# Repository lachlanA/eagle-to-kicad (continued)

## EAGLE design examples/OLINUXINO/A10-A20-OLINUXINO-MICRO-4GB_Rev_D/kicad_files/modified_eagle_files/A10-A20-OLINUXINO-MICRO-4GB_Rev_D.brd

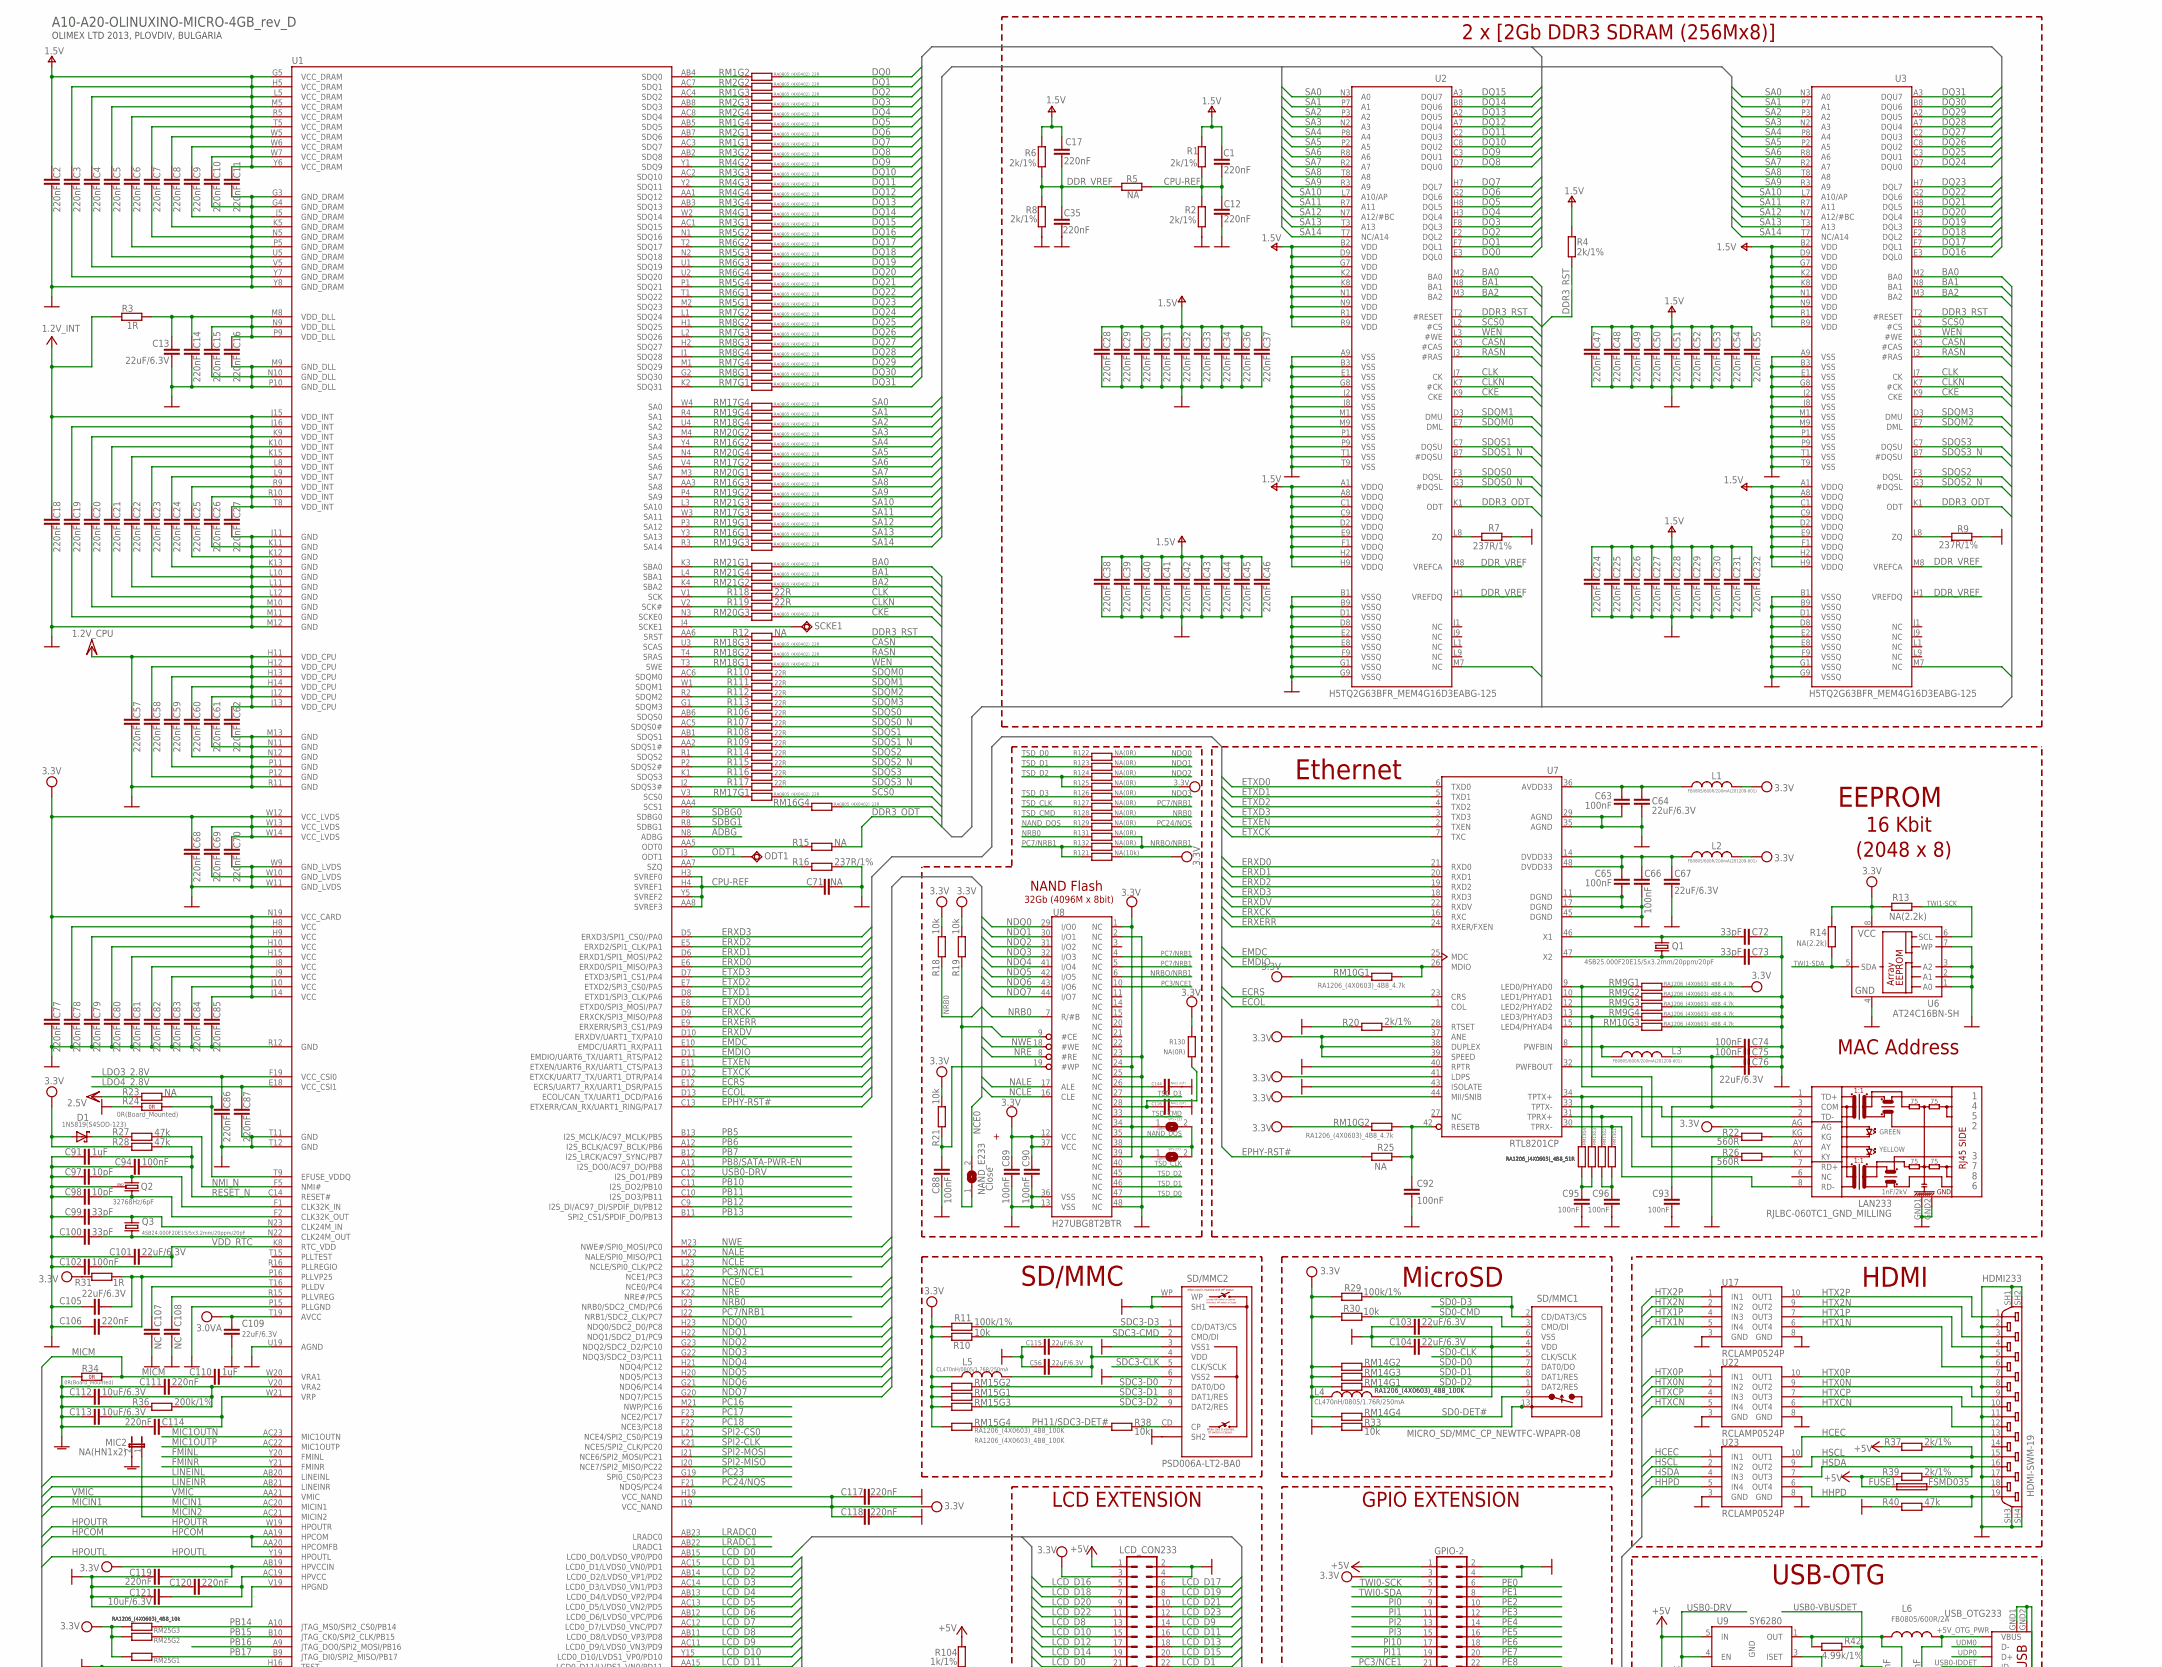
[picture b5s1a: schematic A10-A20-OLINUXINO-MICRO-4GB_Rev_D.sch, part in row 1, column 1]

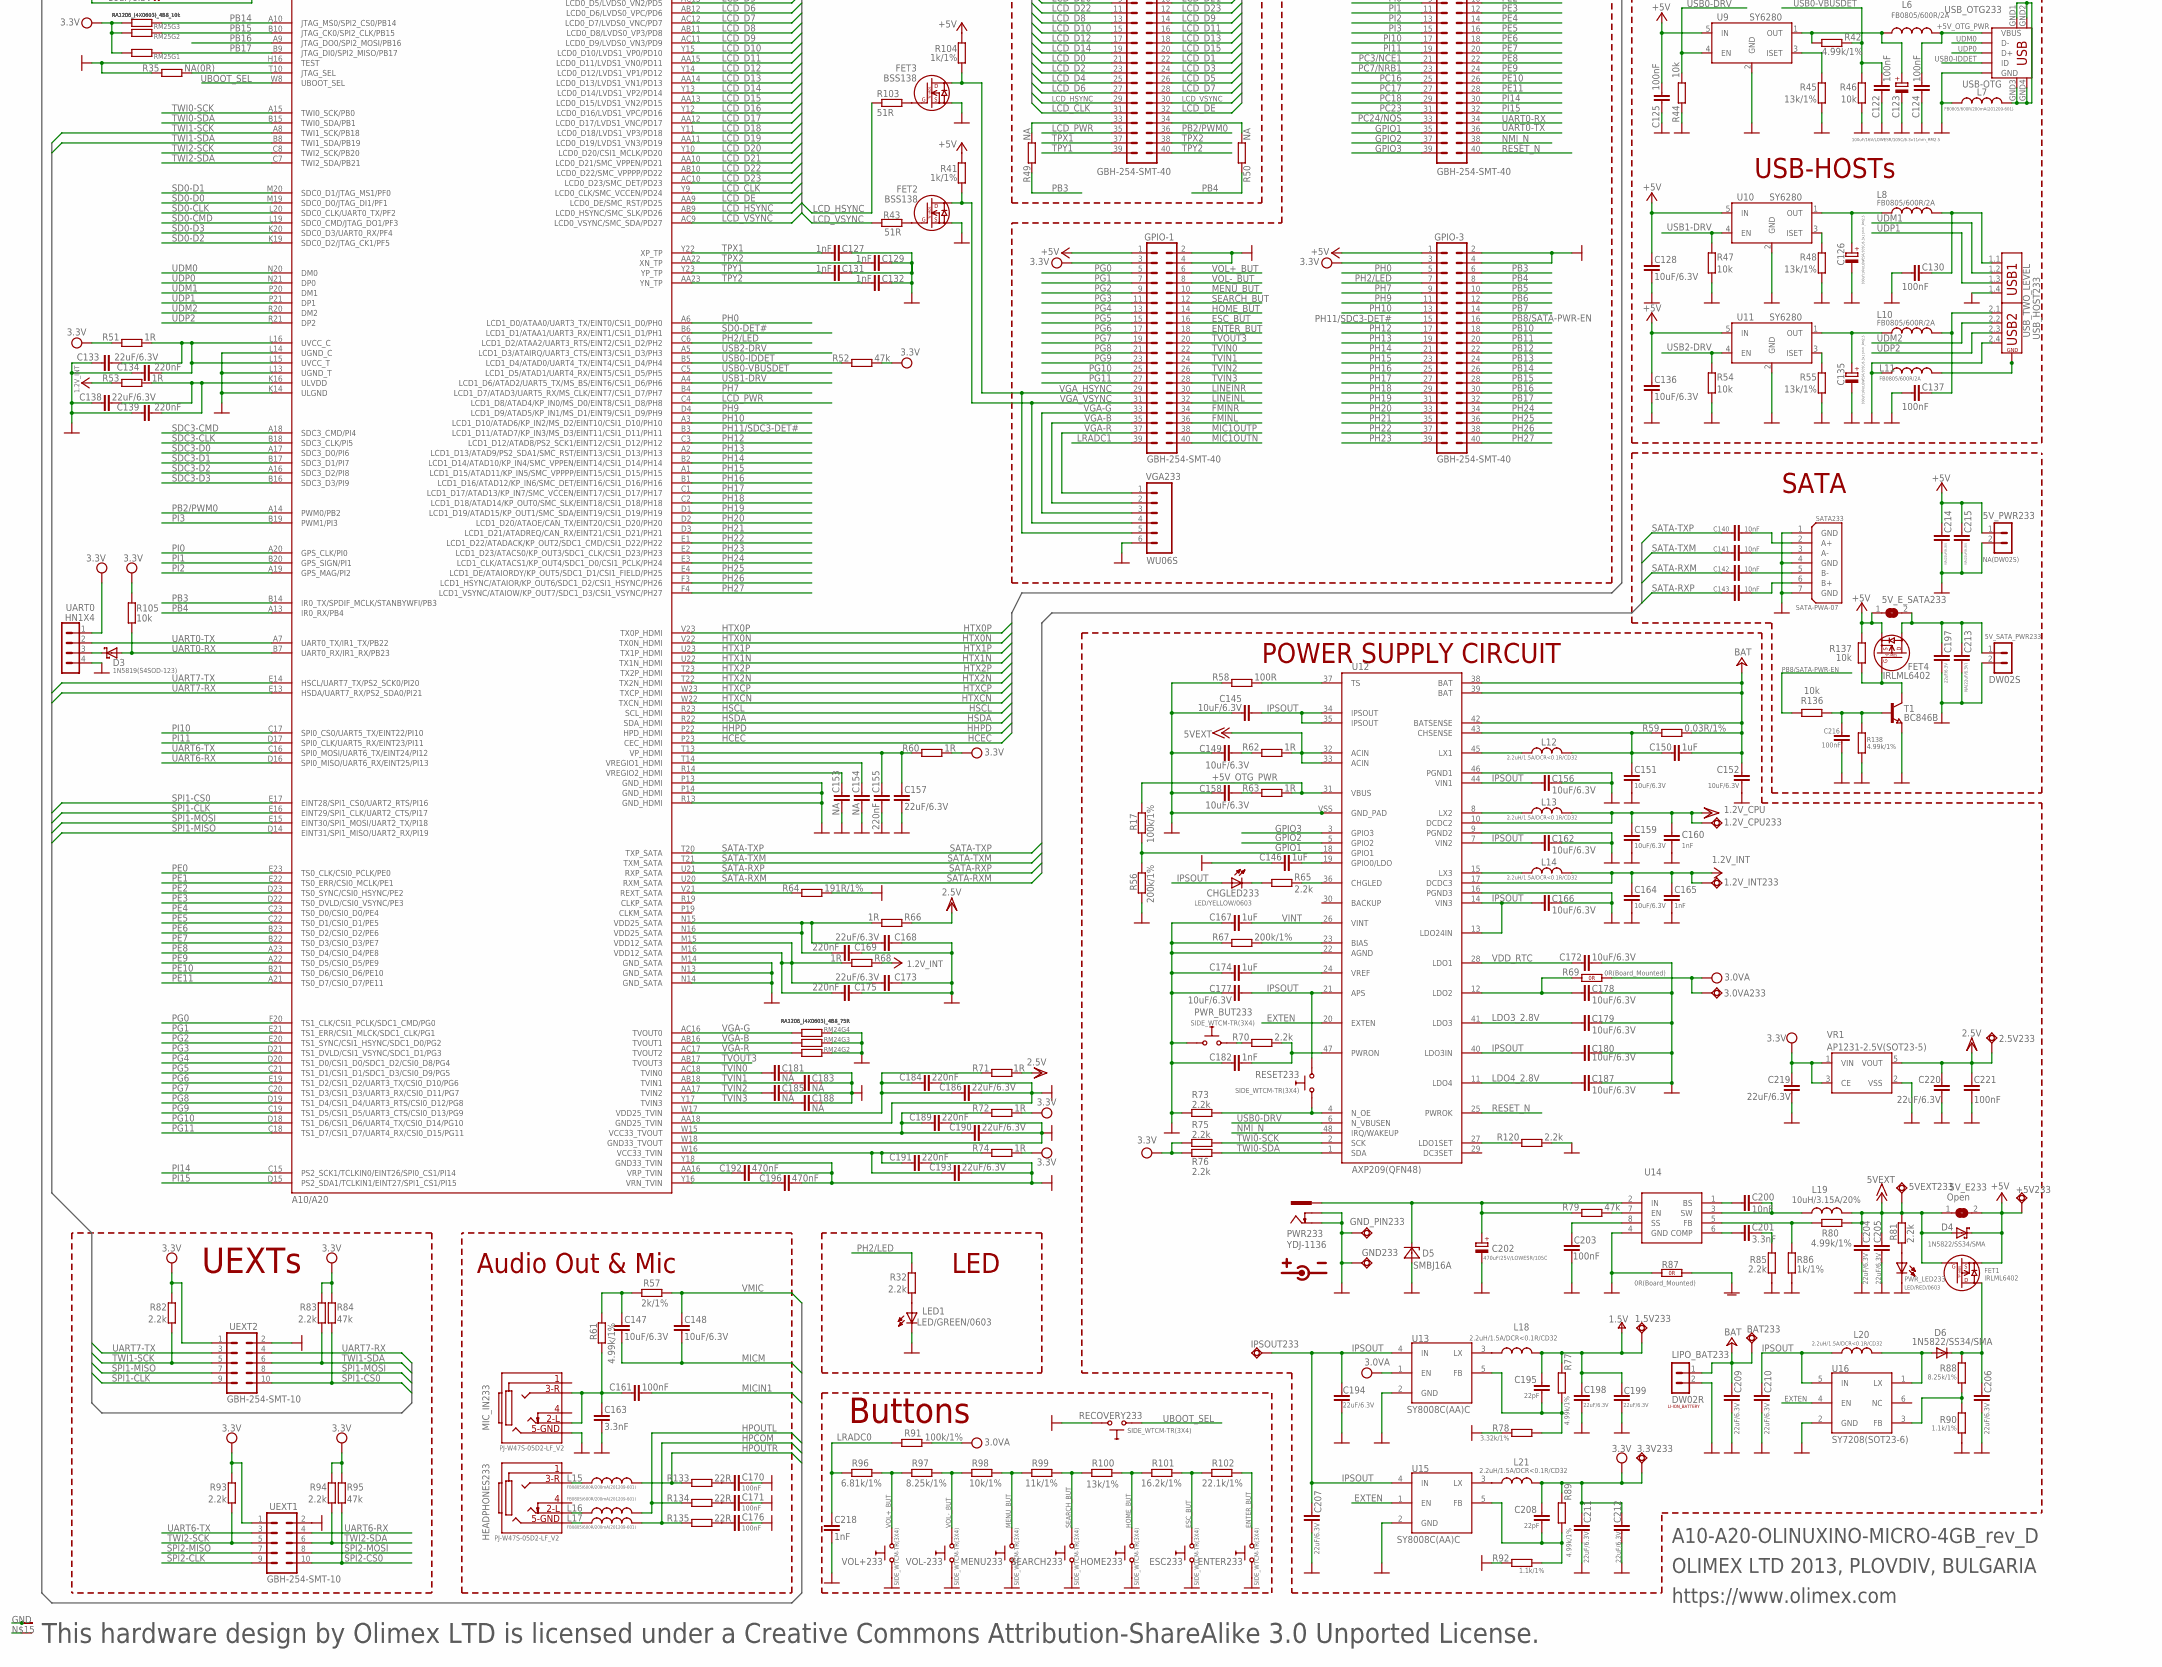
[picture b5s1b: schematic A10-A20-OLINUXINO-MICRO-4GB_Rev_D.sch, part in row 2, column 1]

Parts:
1.2V_CPU233, 1.2V_INT233, 1.5V233, 2.5V233, 3.0VA233, 3.3V233, 5VEXT233: TESTPADTESTPAD_40-ROUND; TESTPAD_40-ROUND
5V_E233: Open; SJ_1_SMALLER
5V_E_SATA233: SJSJ_SMALLER; SJ_1_SMALLER
5V_PWR233: NA(DW02S); DW02S
5V_SATA_PWR233: DW02S
+5V233: TESTPADTESTPAD_40-ROUND; TESTPAD_40-ROUND
BAT233: TESTPADTESTPAD_40-ROUND; TESTPAD_40-ROUND
C1, C4, C6, C8, C9, C12, C16, C17, C20, C28, C29, C30, C31, C32, C33, C34, C35, C36, C37, C38, C39, C40, C41, C42, C43, C44, C45, C46, C47, C48, C49, C50, C51, C52, C53, C54, C55, C58, C81, C111, C114, C117, C118, C119, C120, C224, C225, C226, C227, C228, C229, C230, C231, C232: 220nF; C0603_DWS
C2, C3, C5, C7, C10, C11, C14, C15, C18, C19, C21, C22, C23, C24, C25, C26, C27, C57, C59, C60, C61, C62, C68, C69, C70, C77, C78, C79, C80, C82, C83, C84, C85, C86, C87, C106, C134, C139, C155, C169, C175, C184, C189, C191: 220nF; C0402_TI
C13, C56, C64, C67, C76, C101, C103, C104, C105, C109, C115, C133, C138, C157, C168, C173, C186, C190, C193, C194, C197, C198, C199, C204, C205, C206, C207, C209, C210, C211, C212, C219, C220: 22uF/6.3V; C0603_DWS
C63, C65, C66, C74, C75, C88, C89, C90, C92, C93, C94, C95, C96, C122, C124, C125, C130, C137, C161, C170, C171, C176, C203, C216, C221: 100nF; C0603_DWS
C71, C181, C183, C185, C188: NA; C0603_DWS
C72, C73, C99, C100: 33pF; C0603_DWS
C91, C110, C146, C150, C167, C174: 1uF; C0603_DWS
C97, C98: 10pF; C0603_DWS
C102: 100nF; C0402_TI
C107, C108: NC; C0402_TI
C112, C113, C121, C128, C136, C145, C147, C148, C149, C151, C152, C156, C158, C159, C162, C164, C166, C172, C177, C178, C179, C180, C187: 10uF/6.3V; C0603_DWS
C116, C144: NA(2.2uF); C0603_DWS
C123, C126, C135: 100uF/16V/LOWESR/105C/6.3x11mm_RM2.5; E2,5-6,3
C127, C129, C131, C132, C160, C165, C182, C218: 1nF; C0603_DWS
C140, C141, C142, C143, C200: 10nF; C0402_TI
C153, C154: NA; C0402_TI
C163, C201: 3.3nF; C0603_DWS
C192, C196: 470nF; C0603_DWS
C195, C208: 22pF; C0603_DWS
C202: 470uF/25V/LOWESR/105C; E5-10,5
C213, C214, C215: NA(22uF/6.3V); C0603_DWS
CHGLED233: LED/YELLOW/0603; LED-0603
D1, D3: 1N5819(S4SOD-123); SOD-123
D4: 1N5822/SS34/SMA; MLL-41
D5: SMBJ16A; DO214AA
D6: 1N5822/SS34/SMA; MELF-MLL41
ENTER233: SIDE_WTCM-TR(3X4); SW_TAKT3X4
ESC233: SIDE_WTCM-TR(3X4); SW_TAKT3X4
FET1, FET4: IRLML6402; SOT23
FET2, FET3: BSS138; SOT23
FUSE1: FSMD035; 1206
GND233: TESTPADTESTPAD_40-ROUND; TESTPAD_40-ROUND
GND_PIN233: TESTPAD3; TEST_PAD40/70/SQUARE
GPIO-1, GPIO-2, GPIO-3: GBH-254-SMT-40; ML40-MALE(GBH-254-SMT-40)
HDMI233: HDMI-SWM-19
HEADPHONES233: PJ-W47S-05D2-LF_V2; PJ-W47S-05D2-LF_5PIN_V2
HOME233: SIDE_WTCM-TR(3X4); SW_TAKT3X4
IPSOUT233: TESTPADTESTPAD_40-ROUND; TESTPAD_40-ROUND
L1, L2, L3, L7, L15, L16, L17: FB0805/600R/200mA(201209-601); L0805_5MIL_DWS
L4, L5: CL470nH/0805/1.76R/250mA; L0805_5MIL_DWS
L6, L8, L10, L11: FB0805/600R/2A; L0805_5MIL_DWS
L12, L13, L14, L18, L20, L21: 2.2uH/1.5A/DCR<0.1R/CD32; CD32
L19: 10uH/3.15A/20%; 8X8MM_3131
LAN233: RJLBC-060TC1_GND_MILLING; RJLBC-060TC1_MILLING
LCD_CON233: GBH-254-SMT-40; ML40-MALE(GBH-254-SMT-40)
LED1: LED/GREEN/0603; LED-0603
LIPO_BAT233: DW02R
MENU233: SIDE_WTCM-TR(3X4); SW_TAKT3X4
MIC2: NA(HN1x2); JP1
MIC_IN233: PJ-W47S-05D2-LF_V2; PJ-W47S-05D2-LF_5PIN_V2
NAND_E233: Close; SJ_1_SMALLER_CLOSE_10MILS
ODT1: TESTPADTESTPAD_40-ROUND; TESTPAD_40-ROUND
PWR233: YDJ-1136; PWR_JACK_UNI_MILLING
PWR_BUT233: SIDE_WTCM-TR(3X4); SW_TAKT3X4
PWR_LED233: LED/RED/0603; LED-0603
Q1: 4SB25.000F20E15/5x3.2mm/20ppm/20pF; HCX-4S
Q2: 32768Hz/6pF; TC26H_3_REPAIR_SMD
Q3: 4SB24.000F20E15/5x3.2mm/20ppm/20pF; HCX-4S
R1, R2, R4, R6, R8, R20, R37, R39, R57: 2k/1%; R0603_5MIL_DWS
R3, R31, R51, R53, R60, R62, R63, R66, R68, R71, R72, R74: 1R; R0603_5MIL_DWS
R5, R23, R25, R49, R50: NA; R0603_5MIL_DWS
R7, R9, R16: 237R/1%; R0603_5MIL_DWS
R10, R18, R19, R21, R30, R33, R38, R44, R46, R47, R54, R105, R136, R137: 10k; R0603_5MIL_DWS
R11, R17, R29, R91: 100k/1%; R0603_5MIL_DWS
R12, R15: NA; R0402_TI
R13, R14: NA(2.2k); R0603_5MIL_DWS
R22, R26: 560R; R0603_5MIL_DWS
R24, R34, R69, R87: 0R(Board_Mounted); 0603_0R
R27, R28, R40, R52, R79, R84, R95: 47k; R0603_5MIL_DWS
R32, R65, R70, R73, R75, R76, R81, R82, R83, R85, R93, R94, R120: 2.2k; R0603_5MIL_DWS
R35: NA(0R); R0603_5MIL_DWS
R36, R56, R67: 200k/1%; R0603_5MIL_DWS
R41, R86, R104: 1k/1%; R0603_5MIL_DWS
R42, R61, R77, R80, R89, R138: 4.99k/1%; R0603_5MIL_DWS
R43, R103: 51R; R0603_5MIL_DWS
R45, R48, R55, R100: 13k/1%; R0603_5MIL_DWS
R58: 100R; R0603_5MIL_DWS
R59: 0.03R/1%; R1206_5MIL_WS
R64: 191R/1%; R0603_5MIL_DWS
R78: 3.32k/1%; R0603_5MIL_DWS
R88, R97: 8.25k/1%; R0603_5MIL_DWS
R90, R92: 1.1k/1%; R0603_5MIL_DWS
R96: 6.81k/1%; R0603_5MIL_DWS
R98: 10k/1%; R0603_5MIL_DWS
R99: 11k/1%; R0603_5MIL_DWS
R101: 16.2k/1%; R0603_5MIL_DWS
R102: 22.1k/1%; R0603_5MIL_DWS
R106, R107, R108, R109, R110, R111, R112, R113, R114, R115, R116, R117, R118, R119, R133, R134, R135: 22R; R0402_TI
R121: NA(10k); R0603_5MIL_DWS
R122, R123, R124, R125, R126, R127, R128, R129, R130, R131, R132: NA(0R); R0402_TI
RECOVERY233: SIDE_WTCM-TR(3X4); SW_TAKT3X4
RESET233: SIDE_WTCM-TR(3X4); SW_TAKT3X4
RM1, RM2, RM3, RM4, RM5, RM6, RM7, RM8, RM16, RM17, RM18, RM19, RM20, RM21: RA0805_(4X0402)_22R; R_MATRIX_4_0402_25X625
RM9, RM10: RA1206_(4X0603)_4B8_4.7k; R_MATRIX_4
RM13: RA1206_(4X0603)_4B8_51R; R_MATRIX_4
RM14, RM15: RA1206_(4X0603)_4B8_100K; R_MATRIX_4
RM24: RA1206_(4X0603)_4B8_75R; R_MATRIX_4
RM25: RA1206_(4X0603)_4B8_10k; R_MATRIX_4
SATA233: SATA-PWA-07
SCKE1: TESTPADTESTPAD_40-ROUND; TESTPAD_40-ROUND
SD/MMC1: MICRO_SD/MMC_CP_NEWTFC-WPAPR-08; TFC-WPAPR-08
SD/MMC2: PSD006A-LT2-BA0; SD_CARD
SEARCH233: SIDE_WTCM-TR(3X4); SW_TAKT3X4
T1: BC846B; SOT23
U1: A10/A20; TFBGA441
U2, U3: H5TQ2G63BFR_MEM4G16D3EABG-125; FBGA96_MEM
U6: AT24C16BN-SH; SO-08MN
U7: RTL8201CP; LQFP48
U8: H27UBG8T2BTR; TSOP48
U9, U10, U11: SY6280; SOT23-5
U12: AXP209(QFN48); QFN48
U13, U15: SY8008C(AA)C; SOT23-5
U14: MP1482DS; SOIC8
U16: SY7208(SOT23-6); SOT23-6
U17, U22, U23: RCLAMP0524P; SLP2510P8
UART0: HN1X4
UEXT1, UEXT2: GBH-254-SMT-10; ML10_S
USB_HOST233: USB_TWO_LEVEL
USB_OTG233: USB-OTG; USB_MINI_9PIN
VGA233: WU06S; CON1.27MM-6-SMALL_ICSP
VOL+233: SIDE_WTCM-TR(3X4); SW_TAKT3X4
VOL-233: SIDE_WTCM-TR(3X4); SW_TAKT3X4
VPS+233: Open; SJ_1_SMALLER
VPS-233: Open; SJ_1_SMALLER
VP_0, VP_1, VP_2, VP_3, VP_4, VP_5, VP_6, VP_7, VP_9, VP_10, VP_11, VP_12, VP_13, VP_14, VP_15, VP_16, VP_18, VP_19, VP_20, VP_21, VP_22, VP_23, VP_24, VP_25, VP_27, VP_28, VP_29, VP_30, VP_31, VP_32, VP_33, VP_34, VP_36, VP_37, VP_38, VP_39, VP_40, VP_41, VP_42, VP_44, VP_45, VP_46, VP_47, VP_48, VP_49, VP_54, VP_55, VP_56: VPDEV0; VPAC0
VP_8, VP_17, VP_26, VP_35: VPDEV1; VPAC1
VP_43: VPDEV2; VPAC2
VP_50, VP_51, VP_53: VPDEV3; VPAC3
VP_52: VPDEV4; VPAC4
VR1: AP1231-2.5V(SOT23-5); SOT-23-5

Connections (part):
+5V: 5V_E233.2, 5V_E_SATA233.1, 5V_PWR233.1, +5V233.1, C125.1, C128.1, C136.1, C214.2, C215.2, D4.K (C), FET1.2 (S), FET4.2 (S), FUSE1.1, GPIO-1.1, GPIO-2.1, GPIO-3.1, LCD_CON233.1, R37.2, R39.2, R41.1, R104.1, R137.1, U9.5 (IN), U10.5 (IN), U11.5 (IN)
+5V_OTG_PWR: C124.1, L6.1, R17.1, R63.2, U12.31 (VBUS), USB_OTG233.VBUS
+15V: 5VEXT233.1, 5V_E233.1, C204.1, C205.1, D4.A, FET1.1 (G), L19.2, R62.2, R80.2, R81.1, U12.32 (ACIN), U12.33 (ACIN)
+24V: BAT233.1, C150.2, C152.1, C209.2, LIPO_BAT233.1, R59.2, U12.38 (BAT), U12.39 (BAT), U12.42 (BATSENSE)
ADBG: U1.N8 (ADBG)
BA0: RM21.1.2 (2), U2.M2 (BA0), U3.M2 (BA0)
BA1: RM21.4.2 (2), U2.N8 (BA1), U3.N8 (BA1)
BA2: RM21.2.2 (2), U2.M3 (BA2), U3.M3 (BA2)
CASN: RM18.3.2 (2), U2.K3 (#CAS), U3.K3 (#CAS)
CKE: RM20.3.2 (2), U2.K9 (CKE), U3.K9 (CKE)
CLK: R118.1, U2.J7 (CK), U3.J7 (CK)
CLKN: R119.1, U2.K7 (#CK), U3.K7 (#CK)
CPU-REF: C1.2, C12.2, C71.2, R1.1, R2.2, R5.2, U1.AA8 (SVREF3), U1.H3 (SVREF0), U1.H4 (SVREF1), U1.Y5 (SVREF2)
DDR3_ODT: R15.1, U2.K1 (ODT), U3.K1 (ODT)
DDR3_RST: R4.1, R12.1, U2.T2 (#RESET), U3.T2 (#RESET)
DDR3_SA0: RM17.4.1 (1), U1.W4 (SA0)
DDR3_SA1: RM19.4.1 (1), U1.R4 (SA1)
DDR3_SA2: RM18.4.1 (1), U1.U4 (SA2)
DDR3_SA3: RM20.2.1 (1), U1.M4 (SA3)
DDR3_SA4: RM16.2.1 (1), U1.Y4 (SA4)
DDR3_SA5: RM20.4.1 (1), U1.N4 (SA5)
DDR3_SA6: RM17.2.1 (1), U1.V4 (SA6)
DDR3_SA7: RM20.1.1 (1), U1.M3 (SA7)
DDR3_SA8: RM16.3.1 (1), U1.AA3 (SA8)
DDR3_SA9: RM19.2.1 (1), U1.P4 (SA9)
DDR3_SA10: RM21.3.1 (1), U1.L3 (SA10)
DDR3_SA11: RM17.3.1 (1), U1.W3 (SA11)
DDR3_SA12: RM19.1.1 (1), U1.P3 (SA12)
DDR3_SA13: RM16.1.1 (1), U1.Y3 (SA13)
DDR3_SA14: RM19.3.1 (1), U1.R3 (SA14)
DDR3_SA15: RM16.4.1 (1), U1.AA4 (SCS1)
DDR3_SBA0: RM21.1.1 (1), U1.K3 (SBA0)
DDR3_SBA1: RM21.4.1 (1), U1.L4 (SBA1)
DDR3_SBA2: RM21.2.1 (1), U1.K4 (SBA2)
DDR3_SCAS: RM18.3.1 (1), U1.U3 (SCAS)
DDR3_SCS0: RM17.1.1 (1), U1.V3 (SCS0)
DDR3_SDQM0: R110.2, U1.AC6 (SDQM0)
DDR3_SDQM1: R111.2, U1.W1 (SDQM1)
DDR3_SDQM2: R112.2, U1.R2 (SDQM2)
DDR3_SDQM3: R113.2, U1.G1 (SDQM3)
DDR3_SDQS0: R106.2, U1.AB6 (SDQS0)
DDR3_SDQS0#: R107.2, U1.AC5 (SDQS0#)
DDR3_SDQS1: R108.2, U1.AB1 (SDQS1)
DDR3_SDQS1#: R109.2, U1.AA2 (SDQS1#)
DDR3_SDQS2: R114.2, U1.R1 (SDQS2)
DDR3_SDQS2#: R115.2, U1.P2 (SDQS2#)
DDR3_SDQS3: R116.2, U1.K1 (SDQS3)
DDR3_SDQS3#: R117.2, U1.J2 (SDQS3#)
DDR3_SRAS: RM18.2.1 (1), U1.T4 (SRAS)
DDR3_SWE: RM18.1.1 (1), U1.T3 (SWE)
DDR_VREF: C17.2, C35.2, R5.1, R6.1, R8.2, U2.H1 (VREFDQ), U2.M8 (VREFCA), U3.H1 (VREFDQ), U3.M8 (VREFCA)
DQ0: RM1.2.1 (1), U2.E3 (DQL0)
DQ1: RM2.2.1 (1), U2.F7 (DQL1)
DQ2: RM1.3.1 (1), U2.F2 (DQL2)
DQ3: RM2.3.1 (1), U2.F8 (DQL3)
DQ4: RM2.4.1 (1), U2.H3 (DQL4)
DQ5: RM1.4.1 (1), U2.H8 (DQL5)
DQ6: RM2.1.1 (1), U2.G2 (DQL6)
DQ7: RM1.1.1 (1), U2.H7 (DQL7)
DQ8: RM3.2.1 (1), U2.D7 (DQU0)
DQ9: RM4.2.1 (1), U2.C3 (DQU1)
DQ10: RM3.3.1 (1), U2.C8 (DQU2)
DQ11: RM4.3.1 (1), U2.C2 (DQU3)
DQ12: RM4.4.1 (1), U2.A7 (DQU4)
DQ13: RM3.4.1 (1), U2.A2 (DQU5)
DQ14: RM4.1.1 (1), U2.B8 (DQU6)
DQ15: RM3.1.1 (1), U2.A3 (DQU7)
DQ16: RM5.2.1 (1), U3.E3 (DQL0)
DQ17: RM6.2.1 (1), U3.F7 (DQL1)
DQ18: RM5.3.1 (1), U3.F2 (DQL2)
DQ19: RM6.3.1 (1), U3.F8 (DQL3)
DQ20: RM6.4.1 (1), U3.H3 (DQL4)
DQ21: RM5.4.1 (1), U3.H8 (DQL5)
DQ22: RM6.1.1 (1), U3.G2 (DQL6)
DQ23: RM5.1.1 (1), U3.H7 (DQL7)
DQ24: RM7.2.1 (1), U3.D7 (DQU0)
DQ25: RM8.2.1 (1), U3.C3 (DQU1)
DQ26: RM7.3.1 (1), U3.C8 (DQU2)
DQ27: RM8.3.1 (1), U3.C2 (DQU3)
DQ28: RM8.4.1 (1), U3.A7 (DQU4)
DQ29: RM7.4.1 (1), U3.A2 (DQU5)
DQ30: RM8.1.1 (1), U3.B8 (DQU6)
DQ31: RM7.1.1 (1), U3.A3 (DQU7)
ECOL: U1.D13 (ECOL/CAN_TX/UART1_DCD/PA16), U7.1 (COL)
ECRS: U1.E12 (ECRS/UART7_RX/UART1_DSR/PA15), U7.23 (CRS)
EMDC: U1.E10 (EMDC/UART1_RX/PA11), U7.25 (MDC)
EMDIO: RM10.1.1 (1), U1.D11 (EMDIO/UART6_TX/UART1_RTS/PA12), U7.26 (MDIO)
ENTER_BUT: ENTER233.1_1 (1), GPIO-1.18, R102.2
EPHY-RST#: R25.1, U1.C13 (ETXERR/CAN_RX/UART1_RING/PA17)
ERXCK: U1.D9 (ERXCK/SPI3_MISO/PA8), U7.16 (RXC)
ERXD0: U1.E6 (ERXD0/SPI1_MISO/PA3), U7.21 (RXD0)
ERXD1: U1.D6 (ERXD1/SPI1_MOSI/PA2), U7.20 (RXD1)
ERXD2: U1.E5 (ERXD2/SPI1_CLK/PA1), U7.19 (RXD2)
ERXD3: U1.D5 (ERXD3/SPI1_CS0//PA0), U7.18 (RXD3)
ERXDV: U1.D10 (ERXDV/UART1_TX/PA10), U7.22 (RXDV)
ERXERR: U1.E9 (ERXERR/SPI3_CS1/PA9), U7.24 (RXER/FXEN)
ESC_BUT: ESC233.1_1 (1), GPIO-1.16, R101.2, R102.1
ETXCK: U1.D12 (ETXCK/UART7_TX/UART1_DTR/PA14), U7.7 (TXC)
ETXD0: U1.E8 (ETXD0/SPI3_MOSI/PA7), U7.6 (TXD0)
ETXD1: U1.D8 (ETXD1/SPI3_CLK/PA6), U7.5 (TXD1)
ETXD2: U1.E7 (ETXD2/SPI3_CS0/PA5), U7.4 (TXD2)
ETXD3: U1.D7 (ETXD3/SPI1_CS1/PA4), U7.3 (TXD3)
ETXEN: U1.E11 (ETXEN/UART6_RX/UART1_CTS/PA13), U7.2 (TXEN)
EXTEN: U12.20 (EXTEN), U15.1 (EN), U16.4 (EN)
FMINL: GPIO-1.36, U1.Y20 (FMINL)
FMINR: GPIO-1.34, U1.Y21 (FMINR)
GND: 5V_PWR233.2, 5V_SATA_PWR233.2, C2.1, C3.1, C4.1, C5.1, C6.1, C7.1, C8.1, C9.1, C10.1, C11.1, C12.1, C13.1, C14.1, C15.1, C16.1, C18.1, C19.1, C20.1, C21.1, C22.1, C23.1, C24.1, C25.1, C26.1, C27.1, C28.1, C29.1, C30.1, C31.1, C32.1, C33.1, C34.1, C35.1, C36.1, C37.1, C38.1, C39.1, C40.1, C41.1, C42.1, C43.1, C44.1, C45.1, C46.1, C47.1, C48.1, C49.1, C50.1, C51.1, C52.1, C53.1, C54.1, C55.1, C56.1, C57.1, C58.1, C59.1, C60.1, C61.1, C62.1, C63.1, C64.1, C65.1, C66.1, C67.1, C68.1, C69.1, C70.1, C71.1, C72.1, C73.1, C74.2, C75.2, C76.2, C77.1, C78.1, C79.1, C80.1, C81.1, C82.1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
GNDA: C111.1, C112.1, C113.1, C114.1, MIC2.2, R34.1 (1.1), R36.2, R87.2 (1.2)
GPIO1: GPIO-2.35, R17.2, R56.1, U12.18 (GPIO1)
GPIO2: GPIO-2.37, U12.5 (GPIO2)
GPIO3: GPIO-2.39, U12.3 (GPIO3)
HCEC: HDMI233.13, U1.P23 (CEC_HDMI), U23.1 (IN1), U23.10 (OUT1)
HDMI_5V_SOURCE: FUSE1.2, HDMI233.18
HHPD: HDMI233.19, R40.1, U1.P22 (HPD_HDMI), U23.5 (IN4), U23.6 (OUT4)
HOME_BUT: GPIO-1.14, HOME233.1_1 (1), R100.2, R101.1
HPCOM: L17.1, R135.2, U1.AA19 (HPCOM), U1.AA20 (HPCOMFB)
HPOUTL: L16.1, R134.2, U1.Y19 (HPOUTL)
HPOUTR: L15.1, R133.2, U1.W19 (HPOUTR)
HSCL: HDMI233.15, R37.1, U1.R23 (SCL_HDMI), U23.2 (IN2), U23.9 (OUT2)
HSDA: HDMI233.16, R39.1, U1.R22 (SDA_HDMI), U23.4 (IN3), U23.7 (OUT3)
HTX0N: HDMI233.9, U1.V22 (TX0N_HDMI), U22.2 (IN2), U22.9 (OUT2)
HTX0P: HDMI233.7, U1.V23 (TX0P_HDMI), U22.1 (IN1), U22.10 (OUT1)
HTX1N: HDMI233.6, U1.U22 (TX1N_HDMI), U17.5 (IN4), U17.6 (OUT4)
HTX1P: HDMI233.4, U1.U23 (TX1P_HDMI), U17.4 (IN3), U17.7 (OUT3)
HTX2N: HDMI233.3, U1.T22 (TX2N_HDMI), U17.2 (IN2), U17.9 (OUT2)
HTX2P: HDMI233.1, U1.T23 (TX2P_HDMI), U17.1 (IN1), U17.10 (OUT1)
HTXCN: HDMI233.12, U1.W22 (TXCN_HDMI), U22.5 (IN4), U22.6 (OUT4)
HTXCP: HDMI233.10, U1.W23 (TXCP_HDMI), U22.4 (IN3), U22.7 (OUT3)
IPSOUT: C145.2, C156.1, C162.1, C166.1, C177.2, C180.1, C194.1, C207.1, C210.2, CHGLED233.A, IPSOUT233.1, L20.1, RESET233.1_1 (1), U12.7 (VIN2), U12.13 (LDO24IN), U12.14 (VIN3), U12.21 (APS), U12.34 (IPSOUT), U12.35 (IPSOUT), U12.40 (LDO3IN), U12.44 (VIN1), U13.4 (IN), U15.4 (IN), U16.5 (IN)
LCD_CLK: LCD_CON233.31, U1.Y9 (LCD0_CLK/SMC_VCCEN/PD24)
LCD_D0: LCD_CON233.21, U1.AB15 (LCD0_D0/LVDS0_VP0/PD0)
LCD_D1: LCD_CON233.22, U1.AC15 (LCD0_D1/LVDS0_VN0/PD1)
LCD_D2: LCD_CON233.23, U1.AB14 (LCD0_D2/LVDS0_VP1/PD2)
LCD_D3: LCD_CON233.24, U1.AC14 (LCD0_D3/LVDS0_VN1/PD3)
LCD_D4: LCD_CON233.25, U1.AB13 (LCD0_D4/LVDS0_VP2/PD4)
LCD_D5: LCD_CON233.26, U1.AC13 (LCD0_D5/LVDS0_VN2/PD5)
LCD_D6: LCD_CON233.27, U1.AB12 (LCD0_D6/LVDS0_VPC/PD6)
LCD_D7: LCD_CON233.28, U1.AC12 (LCD0_D7/LVDS0_VNC/PD7)
LCD_D8: LCD_CON233.13, U1.AB11 (LCD0_D8/LVDS0_VP3/PD8)
LCD_D9: LCD_CON233.14, U1.AC11 (LCD0_D9/LVDS0_VN3/PD9)
LCD_D10: LCD_CON233.15, U1.Y15 (LCD0_D10/LVDS1_VP0/PD10)
LCD_D11: LCD_CON233.16, U1.AA15 (LCD0_D11/LVDS1_VN0/PD11)
LCD_D12: LCD_CON233.17, U1.Y14 (LCD0_D12/LVDS1_VP1/PD12)
LCD_D13: LCD_CON233.18, U1.AA14 (LCD0_D13/LVDS1_VN1/PD13)
LCD_D14: LCD_CON233.19, U1.Y13 (LCD0_D14/LVDS1_VP2/PD14)
LCD_D15: LCD_CON233.20, U1.AA13 (LCD0_D15/LVDS1_VN2/PD15)
LCD_D16: LCD_CON233.5, U1.Y12 (LCD0_D16/LVDS1_VPC/PD16)
LCD_D17: LCD_CON233.6, U1.AA12 (LCD0_D17/LVDS1_VNC/PD17)
LCD_D18: LCD_CON233.7, U1.Y11 (LCD0_D18/LVDS1_VP3/PD18)
LCD_D19: LCD_CON233.8, U1.AA11 (LCD0_D19/LVDS1_VN3/PD19)
LCD_D20: LCD_CON233.9, U1.Y10 (LCD0_D20/CSI1_MCLK/PD20)
LCD_D21: LCD_CON233.10, U1.AA10 (LCD0_D21/SMC_VPPEN/PD21)
LCD_D22: LCD_CON233.11, U1.AB10 (LCD0_D22/SMC_VPPPP/PD22)
LCD_D23: LCD_CON233.12, U1.AC10 (LCD0_D23/SMC_DET/PD23)
LCD_DE: LCD_CON233.32, U1.AA9 (LCD0_DE/SMC_RST/PD25)
LCD_HSYNC: LCD_CON233.29, R103.1, U1.AB9 (LCD0_HSYNC/SMC_SLK/PD26)
LCD_PWR: LCD_CON233.35, U1.C4 (LCD1_D8/ATAD4/KP_IN0/MS_D0/EINT8/CSI1_D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)
LCD_VSYNC: LCD_CON233.30, R43.1, U1.AC9 (LCD0_VSYNC/SMC_SDA/PD27)
LDO3_2.8V: C86.2, C179.1, U1.F19 (VCC_CSI0), U12.41 (LDO3)
LDO4_2.8V: C87.2, C187.1, U1.E18 (VCC_CSI1), U12.11 (LDO4)
LINEINL: GPIO-1.32, U1.AB20 (LINEINL)
LINEINR: GPIO-1.30, U1.AB21 (LINEINR)
LRADC0: C218.1, R91.2, R96.1, U1.AB23 (LRADC0)
LRADC1: GPIO-1.39, U1.AB22 (LRADC1)
MENU_BUT: GPIO-1.10, MENU233.1_1 (1), R98.2, R99.1
MIC1OUTN: GPIO-1.40, U1.AC23 (MIC1OUTN)
MIC1OUTP: GPIO-1.38, U1.AC22 (MIC1OUTP)
MICIN1: C161.2, U1.AC20 (MICIN1)
MICIN2: MIC2.1, U1.AC21 (MICIN2)
MICM: C110.1, C147.1, C148.1, R34.2 (1.2)
unnamed: C120.2, C121.2, U1.AC19 (HPVCC)
unnamed: R16.2, U1.AA7 (SZQ)
unnamed: R7.2, U2.L8 (ZQ)
unnamed: R65.2, U12.36 (CHGLED)
unnamed: R9.2, U3.L8 (ZQ)
unnamed: R20.2, U7.28 (RTSET)
unnamed: D3.C, UART0.3
unnamed: L18.1, U13.3 (LX)
unnamed: C146.2, U12.19 (GPIO0/LDO)
unnamed: D1.C, R27.2
unnamed: FET2.1 (G), R43.2
unnamed: R120.1, U12.27 (LDO1SET)
unnamed: RM10.3.1 (1), U7.15 (LED4/PHYAD4)
unnamed: C144.1, U8.26 (NC)
unnamed: C161.1, C163.2, MIC_IN233.2, MIC_IN233.3, R61.2
unnamed: C216.1, R136.1, R138.2, T1.1 (B)
unnamed: FET4.1 (G), R137.2, T1.3 (C)
unnamed: C195.2, R77.2, R78.1, U13.5 (FB)
unnamed: C116.1, R130.2, U8.28 (NC)
unnamed: C63.2, C64.2, L1.1, U7.36 (AVDD33)
unnamed: HEADPHONES233.5, L17.2
unnamed: C206.1, D6.1 (C), FET1.3 (D), R88.2
unnamed: 5V_E_SATA233.2, 5V_SATA_PWR233.1, C197.2, C213.2, FET4.3 (D)
unnamed: HEADPHONES233.2, L16.2
unnamed: HEADPHONES233.3, L15.2
unnamed: FET3.1 (G), R103.2
unnamed: C178.1, R69.2 (1.2), U12.12 (LDO2)
unnamed: C202.+, D5.C, PWR233.+, R79.1, U14.2 (IN)
unnamed: C92.2, R25.2, RM10.2.1 (1), U7.42 (RESETB)
unnamed: C96.2, RM13.1.1 (1), RM13.2.1 (1)
unnamed: C171.2, R134.1
unnamed: C176.2, R135.1
unnamed: C203.1, U14.8 (SS)
unnamed: R79.2, U14.7 (EN)
unnamed: PWR_BUT233.1_1 (1), R70.1
unnamed: LAN233.1 (TD+), RM13.4.2 (2), U7.34 (TPTX+)
unnamed: LAN233.2 (TD-), RM13.3.2 (2), U7.33 (TPTX-)
unnamed: LAN233.7 (RD+), RM13.2.2 (2), U7.31 (TPRX+)
unnamed: C192.2, U1.AA16 (VRP_TVIN)
unnamed: CHGLED233.C, R65.1
unnamed: C170.2, R133.1
unnamed: LAN233.8 (RD-), RM13.1.2 (2), U7.30 (TPRX-)
unnamed: C200.1, U14.1 (BS)
unnamed: C95.2, RM13.3.1 (1), RM13.4.1 (1)
unnamed: RM9.2.2 (2), U7.10 (LED1/PHYAD1)
unnamed: C200.2, L19.1, U14.3 (SW)
unnamed: RM9.3.2 (2), U7.12 (LED2/PHYAD2)
unnamed: LAN233.KG, R22.1
unnamed: LAN233.AY, RM9.4.2 (2), U7.13 (LED3/PHYAD3)
unnamed: C74.1, L3.1, U7.8 (PWFBIN)
unnamed: C75.1, C76.1, C93.2, L3.2, LAN233.3 (COM), U7.32 (PWFBOUT)
unnamed: LAN233.KY, R26.1
unnamed: R33.1, SD/MMC1.10 (PACK1), SD/MMC1.11 (PACK2), SD/MMC1.12 (PACK3), SD/MMC1.13 (PACK4)
unnamed: C201.1, U14.6 (COMP)
unnamed: C201.2, R85.1
unnamed: R80.1, R86.1, U14.5 (FB)
unnamed: L21.1, U15.3 (LX)
unnamed: C208.2, R89.2, R92.1, U15.5 (FB)
unnamed: C65.2, C66.2, C67.2, L2.1, U7.14 (DVDD33), U7.48 (DVDD33)
unnamed: R22.2, RM9.1.2 (2), U7.9 (LED0/PHYAD0)
unnamed: U8.38 (NC), VPS+233.2, VPS-233.2
unnamed: C155.1, C157.2, R60.2, U1.T13 (VP_HDMI)
unnamed: C153.1, U1.R14 (VREGIO2_HDMI)
unnamed: C154.1, U1.T14 (VREGIO1_HDMI)
unnamed: R23.1, R24.2 (1.2), U1.T9 (EFUSE_VDDQ)
unnamed: C105.2, C106.2, R31.1, U1.P16 (PLLVP25)
unnamed: C97.2, Q2.1, U1.F1 (CLK32K_IN)
unnamed: R45.2, U9.3 (ISET)
unnamed: C123.+, L6.2, R42.2, U9.1 (OUT)
unnamed: R48.2, U10.3 (ISET)
unnamed: C133.2, C134.2, R51.1, U1.L15 (UVCC_T), U1.L16 (UVCC_C)
unnamed: C138.2, C139.2, R53.1, U1.K16 (ULVDD)
unnamed: C140.2, SATA233.2 (A+)
unnamed: C130.1, L8.2, USB_HOST233.1.1
unnamed: C141.2, SATA233.3 (A-)
unnamed: C142.2, SATA233.5 (B-)
unnamed: C143.2, SATA233.6 (B+)
unnamed: C107.2, U1.T16 (PLLDV)
unnamed: C98.2, Q2.2, U1.F2 (CLK32K_OUT)
unnamed: R64.2, U1.V21 (REXT_SATA)
unnamed: R67.2, U12.23 (BIAS)
unnamed: C108.2, U1.R15 (PLLVREG)
unnamed: C113.2, C114.2, U1.W21 (VRP)
unnamed: D6.2 (A), L20.2, U16.1 (LX)
unnamed: C88.2, R21.2, U8.19 (#WP)
unnamed: R58.2, U12.37 (TS)
unnamed: R88.1, R90.1, U16.3 (FB)
unnamed: L12.1, U12.45 (LX1)
unnamed: C150.1, C151.1, L12.2, R59.1, U12.43 (CHSENSE)
unnamed: PWR_LED233.A, R81.2
unnamed: L13.1, U12.8 (LX2)
unnamed: L14.1, U12.15 (LX3)
unnamed: C174.2, U12.24 (VREF)
unnamed: C110.2, U1.W20 (VRA1)
unnamed: C149.2, R62.1
unnamed: C158.2, R63.1
unnamed: R55.2, U11.3 (ISET)
unnamed: C182.2, R70.2, U12.47 (PWRON)
unnamed: R73.2, RESET233.2_1 (0), U12.4 (N_OE)
unnamed: R38.1, SD/MMC2.CD (CP)
unnamed: C111.2, C112.2, R36.1, U1.V20 (VRA2)
unnamed: C147.2, R57.1, R61.1
unnamed: R35.1, U1.T10 (JTAG_SEL)
unnamed: C168.2, C169.2, R66.1, U1.N15 (VDD25_SATA), U1.N16 (VDD25_SATA)
unnamed: C126.+, L8.1, U10.1 (OUT)
unnamed: L11.2, USB_HOST233.GND1, USB_HOST233.GND2, USB_HOST233.GND3, USB_HOST233.GND4
unnamed: C137.1, L10.2, USB_HOST233.2.1
unnamed: C135.+, L10.1, U11.1 (OUT)
unnamed: C173.2, C175.2, R68.1, U1.M15 (VDD12_SATA), U1.M16 (VDD12_SATA)
unnamed: C13.2, C14.2, C15.2, C16.2, R3.1, U1.M8 (VDD_DLL), U1.N9 (VDD_DLL), U1.P9 (VDD_DLL)
unnamed: C191.1, C193.2, R74.2, U1.W16 (VCC33_TVIN)
unnamed: C189.1, C190.2, R72.2, U1.W15 (VCC33_TVOUT)
unnamed: C184.1, C186.2, R71.2, U1.W17 (VDD25_TVIN)
unnamed: C196.2, U1.Y16 (VRN_TVIN)
unnamed: LCD_CON233.33, R49.1
unnamed: LCD_CON233.34, R50.1
unnamed: LED1.A, R32.2
unnamed: NAND_E233.1, R19.2, U8.9 (#CE)
unnamed: L7.2, USB_OTG233.GND1, USB_OTG233.GND2, USB_OTG233.GND3, USB_OTG233.GND4
NALE: U1.M22 (NALE/SPI0_MISO/PC1), U8.17 (ALE)
NAND_DQS: R129.2, U8.35 (NC)
NCE0: NAND_E233.2, U1.K23 (NCE0/PC4)
NCLE: U1.L23 (NCLE/SPI0_CLK/PC2), U8.16 (CLE)
NDQ0: R122.1, U1.H23 (NDQ0/SDC2_D0/PC8), U8.29 (I/O0)
NDQ1: R123.1, U1.H22 (NDQ1/SDC2_D1/PC9), U8.30 (I/O1)
NDQ2: R124.1, U1.G23 (NDQ2/SDC2_D2/PC10), U8.31 (I/O2)
NDQ3: R126.1, U1.G22 (NDQ3/SDC2_D3/PC11), U8.32 (I/O3)
NDQ4: U1.H21 (NDQ4/PC12), U8.41 (I/O4)
NDQ5: U1.H20 (NDQ5/PC13), U8.42 (I/O5)
NDQ6: U1.G21 (NDQ6/PC14), U8.43 (I/O6)
NDQ7: U1.G20 (NDQ7/PC15), U8.44 (I/O7)
NMI_N: GPIO-2.38, R27.1, U1.F5 (NMI#), U12.48 (IRQ/WAKEUP)
NRB0: R18.2, R128.1, R131.2, U1.J23 (NRB0/SDC2_CMD/PC6), U8.7 (R/#B)
NRBO/NRB1: R131.1, R132.1, U8.6 (NC)
NRE: U1.K22 (NRE#/PC5), U8.8 (#RE)
NWE: U1.M23 (NWE#/SPI0_MOSI/PC0), U8.18 (#WE)
ODT0: R15.2, U1.AA5 (ODT0)
ODT1: ODT1.1, U1.J3 (ODT1)
PB2/PWM0: LCD_CON233.36, U1.A14 (PWM0/PB2)
PB3: GPIO-3.6, R49.2, U1.B14 (IR0_TX/SPDIF_MCLK/STANBYWFI/PB3)
PB4: GPIO-3.8, R50.2, U1.A13 (IR0_RX/PB4)
PB5: GPIO-3.10, U1.B13 (I2S_MCLK/AC97_MCLK/PB5)
PB6: GPIO-3.12, U1.A12 (I2S_BCLK/AC97_BCLK/PB6)
PB7: GPIO-3.14, U1.B12 (I2S_LRCK/AC97_SYNC/PB7)
PB8/SATA-PWR-EN: GPIO-3.16, R136.2, U1.A11 (I2S_DO0/AC97_DO/PB8)
PB10: GPIO-3.18, U1.C11 (I2S_DO2/PB10)
PB11: GPIO-3.20, U1.C10 (I2S_DO3/PB11)
PB12: GPIO-3.22, U1.C9 (I2S_DI/AC97_DI/SPDIF_DI/PB12)
PB13: GPIO-3.24, U1.B11 (SPI2_CS1/SPDIF_DO/PB13)
PB14: GPIO-3.26, RM25.3.1 (1), U1.A10 (JTAG_MS0/SPI2_CS0/PB14)
PB15: GPIO-3.28, RM25.2.1 (1), U1.B10 (JTAG_CK0/SPI2_CLK/PB15)
PB16: GPIO-3.30, U1.A9 (JTAG_DO0/SPI2_MOSI/PB16)
PB17: GPIO-3.32, RM25.1.1 (1), U1.B9 (JTAG_DI0/SPI2_MISO/PB17)
PC3/NCE1: GPIO-2.21, U1.L22 (NCE1/PC3), U8.10 (NC)
PC7/NRB1: GPIO-2.23, R121.2, R127.1, R132.2, U1.J22 (NRB1/SDC2_CLK/PC7), U8.4 (NC), U8.5 (NC)
PC16: GPIO-2.25, U1.M21 (NWP/PC16)
PC17: GPIO-2.27, U1.F23 (NCE2/PC17)
PC18: GPIO-2.29, U1.F22 (NCE3/PC18)
PC23: GPIO-2.31, U1.G19 (SPI0_CS0/PC23)
PC24/NQS: GPIO-2.33, R129.1, U1.F21 (NDQS/PC24)
PE0: GPIO-2.6, U1.E23 (TS0_CLK/CSI0_PCLK/PE0)
PE1: GPIO-2.8, U1.E22 (TS0_ERR/CSI0_MCLK/PE1)
PE2: GPIO-2.10, U1.D23 (TS0_SYNC/CSI0_HSYNC/PE2)
PE3: GPIO-2.12, U1.D22 (TS0_DVLD/CSI0_VSYNC/PE3)
PE4: GPIO-2.14, U1.C23 (TS0_D0/CSI0_D0/PE4)
PE5: GPIO-2.16, U1.C22 (TS0_D1/CSI0_D1/PE5)
PE6: GPIO-2.18, U1.B23 (TS0_D2/CSI0_D2/PE6)
PE7: GPIO-2.20, U1.B22 (TS0_D3/CSI0_D3/PE7)
PE8: GPIO-2.22, U1.A23 (TS0_D4/CSI0_D4/PE8)
PE9: GPIO-2.24, U1.A22 (TS0_D5/CSI0_D5/PE9)
PE10: GPIO-2.26, U1.B21 (TS0_D6/CSI0_D6/PE10)
PE11: GPIO-2.28, U1.A21 (TS0_D7/CSI0_D7/PE11)
PG0: GPIO-1.5, U1.F20 (TS1_CLK/CSI1_PCLK/SDC1_CMD/PG0)
PG1: GPIO-1.7, U1.E21 (TS1_ERR/CSI1_MLCK/SDC1_CLK/PG1)
PG2: GPIO-1.9, U1.E20 (TS1_SYNC/CSI1_HSYNC/SDC1_D0/PG2)
PG3: GPIO-1.11, U1.D21 (TS1_DVLD/CSI1_VSYNC/SDC1_D1/PG3)
PG4: GPIO-1.13, U1.D20 (TS1_D0/CSI1_D0/SDC1_D2/CSI0_D8/PG4)
PG5: GPIO-1.15, U1.C21 (TS1_D1/CSI1_D1/SDC1_D3/CSI0_D9/PG5)
PG6: GPIO-1.17, U1.E19 (TS1_D2/CSI1_D2/UART3_TX/CSI0_D10/PG6)
PG7: GPIO-1.19, U1.C20 (TS1_D3/CSI1_D3/UART3_RX/CSI0_D11/PG7)
PG8: GPIO-1.21, U1.D19 (TS1_D4/CSI1_D4/UART3_RTS/CSI0_D12/PG8)
PG9: GPIO-1.23, U1.C19 (TS1_D5/CSI1_D5/UART3_CTS/CSI0_D13/PG9)
PG10: GPIO-1.25, U1.D18 (TS1_D6/CSI1_D6/UART4_TX/CSI0_D14/PG10)
PG11: GPIO-1.27, U1.C18 (TS1_D7/CSI1_D7/UART4_RX/CSI0_D15/PG11)
PH0: GPIO-3.5, U1.A6 (LCD1_D0/ATAA0/UART3_TX/EINT0/CSI1_D0/PH0)
PH2/LED: GPIO-3.7, R32.1, U1.C6 (LCD1_D2/ATAA2/UART3_RTS/EINT2/CSI1_D2/P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)
PH7: GPIO-3.9, U1.B4 (LCD1_D7/ATAD3/UART5_RX/MS_CLK/EINT7/CSI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)
PH9: GPIO-3.11, U1.D4 (LCD1_D9/ATAD5/KP_IN1/MS_D1/EINT9/CSI1_D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)
PH10: GPIO-3.13, U1.A3 (LCD1_D10/ATAD6/KP_IN2/MS_D2/EINT10/CSI1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)
PH11/SDC3-DET#: GPIO-3.15, R38.2, RM15.4.1 (1), U1.B3 (LCD1_D11/ATAD7/KP_IN3/MS_D3/EINT11/CSI1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)
PH12: GPIO-3.17, U1.C3 (LCD1_D12/ATAD8/PS2_SCK1/EINT12/CSI1_D12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)
PH13: GPIO-3.19, U1.A2 (LCD1_D13/ATAD9/PS2_SDA1/SMC_RST/EINT13/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)
PH14: GPIO-3.21, U1.B2 (LCD1_D14/ATAD10/KP_IN4/SMC_VPPEN/EINT14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)
PH15: GPIO-3.23, U1.A1 (LCD1_D15/ATAD11/KP_IN5/SMC_VPPPP/EINT15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)
PH16: GPIO-3.25, U1.B1 (LCD1_D16/ATAD12/KP_IN6/SMC_DET/EINT16/C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)
PH17: GPIO-3.27, U1.C1 (LCD1_D17/ATAD13/KP_IN7/SMC_VCCEN/EINT17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)
PH18: GPIO-3.29, U1.C2 (LCD1_D18/ATAD14/KP_OUT0/SMC_SLK/EINT18/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)
PH19: GPIO-3.31, U1.D1 (LCD1_D19/ATAD15/KP_OUT1/SMC_SDA/EINT19/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)
PH20: GPIO-3.33, U1.D2 (LCD1_D20/ATAOE/CAN_TX/EINT20/CSI1_D20/P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)
PH21: GPIO-3.35, U1.D3 (LCD1_D21/ATADREQ/CAN_RX/EINT21/CSI1_D21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)
PH22: GPIO-3.37, U1.E1 (LCD1_D22/ATADACK/KP_OUT2/SDC1_CMD/CSI1_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)
PH23: GPIO-3.39, U1.E2 (LCD1_D23/ATACS0/KP_OUT3/SDC1_CLK/CSI1_D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)
PH24: GPIO-3.34, U1.E3 (LCD1_CLK/ATACS1/KP_OUT4/SDC1_D0/CSI1_PC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)
PH25: GPIO-3.36, U1.E4 (LCD1_DE/ATAIORDY/KP_OUT5/SDC1_D1/CSI1_F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)
PH26: GPIO-3.38, U1.F3 (LCD1_HSYNC/ATAIOR/KP_OUT6/SDC1_D2/CSI1_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)
PH27: GPIO-3.40, U1.F4 (LCD1_VSYNC/ATAIOW/KP_OUT7/SDC1_D3/CSI1_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)
PI0: GPIO-2.9, U1.A20 (GPS_CLK/PI0)
PI1: GPIO-2.11, U1.B20 (GPS_SIGN/PI1)
PI2: GPIO-2.13, U1.A19 (GPS_MAG/PI2)
PI3: GPIO-2.15, U1.B19 (PWM1/PI3)
PI10: GPIO-2.17, U1.C17 (SPI0_CS0/UART5_TX/EINT22/PI10)
PI11: GPIO-2.19, U1.D17 (SPI0_CLK/UART5_RX/EINT23/PI11)
PI14: GPIO-2.30, U1.C15 (PS2_SCK1/TCLKIN0/EINT26/SPI0_CS1/PI14)
PI15: GPIO-2.32, U1.D15 (PS2_SDA1/TCLKIN1/EINT27/SPI1_CS1/PI15)
RASN: RM18.2.2 (2), U2.J3 (#RAS), U3.J3 (#RAS)
RESET_N: C91.2, C94.2, GPIO-2.40, R28.1, U1.C14 (RESET#), U12.25 (PWROK)
SA0: RM17.4.2 (2), U2.N3 (A0), U3.N3 (A0)
SA1: RM19.4.2 (2), U2.P7 (A1), U3.P7 (A1)
SA2: RM18.4.2 (2), U2.P3 (A2), U3.P3 (A2)
SA3: RM20.2.2 (2), U2.N2 (A3), U3.N2 (A3)
SA4: RM16.2.2 (2), U2.P8 (A4), U3.P8 (A4)
SA5: RM20.4.2 (2), U2.P2 (A5), U3.P2 (A5)
SA6: RM17.2.2 (2), U2.R8 (A6), U3.R8 (A6)
SA7: RM20.1.2 (2), U2.R2 (A7), U3.R2 (A7)
SA8: RM16.3.2 (2), U2.T8 (A8), U3.T8 (A8)
SA9: RM19.2.2 (2), U2.R3 (A9), U3.R3 (A9)
SA10: RM21.3.2 (2), U2.L7 (A10/AP), U3.L7 (A10/AP)
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
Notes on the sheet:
POWER SUPPLY CIRCUIT
LI-ION_BATTERY
2 x [2Gb DDR3 SDRAM (256Mx8)]
MicroSD
UEXTs
Buttons
USB-OTG
USB-HOSTs
NAND Flash
32Gb (4096M x 8bit)
GPIO EXTENSION
LCD EXTENSION
Ethernet
EEPROM
MAC Address
16 Kbit
(2048 x 8)
HDMI
SATA
Audio Out & Mic
LED
SD/MMC
This hardware design by Olimex LTD is licensed under a Creative Commons Attribution-ShareAlike 3.0 Unported License.
A10-A20-OLINUXINO-MICRO-4GB_rev_D
OLIMEX LTD 2013, PLOVDIV, BULGARIA
https://www.olimex.com
